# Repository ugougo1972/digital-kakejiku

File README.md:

# digital-kakejiku

**タイトル**  
digital-kakejiku

**最終更新**  
2026-07-15

**文書版**  
vNext 1.3

**STATUS**  
FINALIZED

**責務**  
本書は digital-kakejiku プロジェクトの入口となる文書であり、プロジェクトの目的、全体構成、開発状況、文書体系への導線を提供する。

**Single Source**  
本書はプロジェクト概要および文書体系の入口を管理する唯一の文書である。詳細仕様は各設計文書を参照し、本書へ重複記載しない。

---

# 対象読者

- プロジェクトオーナー
- ハードウェア設計者
- ソフトウェア設計者
- GAS開発者
- 保守担当者
- 新規参画者

---

# 関連文書

## 前提

- docs/00_PROJECT_CONVENTIONS.md

## 参照

- CURRENT_STATUS.md
- ROADMAP.md

## 関連

- docs/01_HARDWARE_OVERVIEW.md
- docs/02_SOFTWARE_OVERVIEW.md
- docs/03_LOG_FORMAT.md
- docs/04_STATE_MACHINE.md
- docs/05_WIRING_DIAGRAM.md
- docs/06_GAS_API_SPEC.md
- docs/07_DISPLAY_UI_SPEC.md
- docs/08_POWER_ARCHITECTURE.md
- docs/09_SPI_RESOURCE_CONTROL.md
- docs/10_CALENDAR_POEM_SUBSYSTEM.md
- docs/11_SECURITY_MANAGEMENT.md
- docs/12_CONFIGURATION_MANAGEMENT.md
- docs/13_GAS_OPERATION_POLICY.md
- docs/14_SPREADSHEET_SCHEMA.md
- docs/15_GAS_IMPLEMENTATION_GUIDE.md
- docs/16_TESTING_STRATEGY.md
- docs/17_TROUBLESHOOTING.md
- docs/18_GAS_RETRY_STRATEGY.md
- docs/19_GEMINI_PROMPT_SPECIFICATION.md

## 後続

本リポジトリを利用するすべての設計・実装・試験・保守作業

---

# 1. プロジェクト概要

## 1.1 概要

digital-kakejiku は、環境観測、暦情報表示、AIによる詩生成を組み合わせた据置型情報表示システムである。

ESP32マイコンを中心として各種環境センサーから取得した情報を Google Apps Script および Google Spreadsheet に蓄積し、必要に応じて AI による文章生成を行い、7.5inch E-Paper に表示する。

本プロジェクトは長期間の安定運用、保守性、拡張性およびドキュメント駆動開発を重視する。

---

## 1.2 プロジェクト目的

本プロジェクトでは以下を目的とする。

- 環境情報の継続的な観測
- 暦情報の表示
- AI生成コンテンツの活用
- 長期運用可能な据置型システムの構築
- 保守性・拡張性を考慮した設計

---

# 2. システム概要

## 2.1 全体構成

```text
環境センサー
        │
        ▼
XIAO ESP32S3 Plus
        │
     HTTPS
        │
        ▼
Google Apps Script
        │
        ▼
Google Spreadsheet
        │
        ▼
Gemini
        │
        ▼
7.5inch E-Paper
```

各コンポーネントの詳細仕様は個別設計書で管理する。

---

## 2.2 システム構成

本システムは以下の主要コンポーネントで構成される。

### ハードウェア

- 本体基板
- 電源基板
- OLED操作基板

### ソフトウェア

- ESP32 Firmware
- Google Apps Script
- Google Spreadsheet
- Gemini

---

## 2.3 主な特徴

- 据置型観測システム
- UPS電源構成
- 7.5inch E-Paper表示
- Google Apps Script連携
- Google Spreadsheet連携
- AIによる詩生成
- 保守用OLEDコンソール
- モジュール交換可能構造
- ファンレス自然空冷

---

# 3. 開発状況

本書では概要のみを示す。

現在の詳細な進捗、完了状況、課題および開発優先順位は **CURRENT_STATUS.md** を正式情報とする。

現在の開発フェーズは以下のとおりである。

|項目|状態|
|---|---|
|開発フェーズ|IN_PROGRESS|
|電源基板PoC|COMPLETED|
|本体基板設計|IN_PROGRESS|
|筐体設計|IN_PROGRESS|
|GAS実装|IN_PROGRESS|
|文書体系整備|IN_PROGRESS|

---

# 4. システム設計方針

本プロジェクトでは以下の設計方針を採用する。

- ドキュメント駆動開発
- モジュール構成
- 保守性優先
- 拡張性優先
- 長期運用を前提とした設計
- GitHubを正式設計情報とする

設計規約の詳細は **00_PROJECT_CONVENTIONS.md** を参照する。

---

# 5. 文書体系

## 5.1 基準文書

以下の4文書をプロジェクト全体の基準文書とする。

|文書|責務|
|---|---|
|README.md|プロジェクト概要・入口|
|CURRENT_STATUS.md|現在の開発状況|
|ROADMAP.md|中長期開発計画|
|docs/00_PROJECT_CONVENTIONS.md|共通規約|

---

## 5.2 設計文書

|文書|内容|
|---|---|
|01_HARDWARE_OVERVIEW|ハードウェア全体設計|
|02_SOFTWARE_OVERVIEW|ソフトウェア全体設計|
|03_LOG_FORMAT|ログ仕様|
|04_STATE_MACHINE|状態遷移|
|05_WIRING_DIAGRAM|配線仕様|
|06_GAS_API_SPEC|GAS API仕様|
|07_DISPLAY_UI_SPEC|表示仕様|
|08_POWER_ARCHITECTURE|電源設計|
|09_SPI_RESOURCE_CONTROL|SPI資源管理|
|10_CALENDAR_POEM_SUBSYSTEM|暦・詩生成|
|11_SECURITY_MANAGEMENT|セキュリティ|
|12_CONFIGURATION_MANAGEMENT|設定管理|
|13_GAS_OPERATION_POLICY|GAS運用|
|14_SPREADSHEET_SCHEMA|Spreadsheet設計|
|15_GAS_IMPLEMENTATION_GUIDE|GAS実装|
|16_TESTING_STRATEGY|試験方針|
|17_TROUBLESHOOTING|障害対応|
|18_GAS_RETRY_STRATEGY|リトライ設計|
|19_GEMINI_PROMPT_SPECIFICATION|Geminiプロンプト仕様|

---

# 6. リポジトリ運用方針

設計・実装・試験・運用に関する情報は GitHub リポジトリで管理する。

設計変更時は以下の順序で更新する。

1. 設計文書更新
2. 関連文書との整合性確認
3. GitHub反映
4. 実装
5. 試験

設計書より先に実装を変更する運用は行わない。

---

# 7. 開発ロードマップ

本書では概要のみを示す。

詳細なマイルストーン、計画および将来構想は **ROADMAP.md** を正式情報とする。

---

# 8. 現在未定義の事項

以下は本書では定義しない。

- リリース計画
- バージョン採番規則
- Git運用詳細
- ブランチ運用
- Commit Message規則

必要となった時点で関連文書に追加する。

---

# CHANGE LOG

|日付|内容|
|---|---|
|2026-07-15|vNext 1.3として全面刷新。READMEをプロジェクト入口文書へ再設計し、Single Source of Truthに基づきCURRENT_STATUS、ROADMAP、00_PROJECT_CONVENTIONSとの責務を明確化。|
|2026-07-14|初版更新。|

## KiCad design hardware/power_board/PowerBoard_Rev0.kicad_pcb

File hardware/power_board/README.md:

# digital-kakejiku PowerBoard Rev.0

## 1. 位置付け

本データは、digital-kakejiku 電源基板PoCの実測結果と、以下の確定済み構成を基に作成した
**KiCad 10取込用の初期設計データ**です。

```text
USB Type-C
    │
   PTC
    │
  IP5306
    │
DMG2305UX-13
    │
  5V_BUS
    │
 TPS63802
    │
 3.3V_OUT
```

## 2. 重要な注意

本データは **JLCPCBへそのまま発注できる最終製造版ではありません**。

理由は、実際に使用する以下の市販モジュールについて、外形寸法・端子ピッチ・穴径が
リポジトリ文書だけでは確定できないためです。

- USB Type-Cブレークアウト基板
- IP5306モジュール
- TPS63802モジュール
- 18650接続コネクタ
- 本体基板接続用10ピンヘッダーの実装形態

現在のPCBデータでは、これらを汎用2.54 mmピッチのスルーホール部品として仮配置しています。
実物を採寸し、フットプリントを確定してから製造データを生成してください。

## 3. 収録ファイル

|ファイル|用途|
|---|---|
|`PowerBoard_Rev0.sch`|KiCad legacy回路図。KiCad 10で開き、`.kicad_sch`として保存してください。|
|`PowerBoard_Rev0.kicad_pcb`|KiCad PCB初期レイアウト。部品配置・ネット・外形を収録しています。|
|`PowerBoard_Rev0.kicad_pro`|KiCadプロジェクト設定の最小ファイルです。|
|`BOM.csv`|初期部品表です。|
|`NETLIST.csv`|ネット接続表です。|
|`FOOTPRINT_CONFIRMATION.md`|実物採寸が必要な項目の一覧です。|
|`JLCPCB_CHECKLIST.md`|Gerber生成前および発注前の確認表です。|

## 4. KiCad 10での開始手順

1. ZIPを展開します。
2. KiCad 10を起動します。
3. `PowerBoard_Rev0.sch`を回路図エディターで開きます。
4. 変換確認が表示された場合は、KiCad 10形式で保存します。
5. 保存名を `PowerBoard_Rev0.kicad_sch` とします。
6. `PowerBoard_Rev0.kicad_pcb`をPCBエディターで開きます。
7. フットプリント実寸を確認・修正します。
8. 回路図からPCBを更新します。
9. ERC・DRCを実行します。
10. エラーおよび未確認警告が残る状態ではJLCPCBへ発注しません。

## 5. 確定済み10ピン電源インターフェース

|ピン|信号|
|---:|---|
|1|5V_OUT|
|2|5V_GND|
|3|5V_OUT|
|4|5V_GND|
|5|3.3V_OUT|
|6|3.3V_GND|
|7|3.3V_OUT|
|8|Battery_SENSE|
|9|5V_SENSE|
|10|SENSE_GND|

## 6. GND方針

- 5V_GND、3.3V_GND、SENSE_GNDは電源基板上で意図的に別ネットとしています。
- 本体基板側のXIAO近傍で一点接続する設計方針です。
- これは電気的絶縁ではなく、リターン経路整理によるノイズ低減を目的とします。
- 使用モジュール内部でGNDが導通している可能性は、実物の導通測定で確認してください。

## 7. Rev.0で仮定した回路定数

|項目|値|
|---|---:|
|5V_SENSE上側抵抗|150 kΩ|
|5V_SENSE下側抵抗|100 kΩ|
|Battery_SENSE上側抵抗|100 kΩ|
|Battery_SENSE下側抵抗|100 kΩ|
|DMG2305UX Gate抵抗|100 kΩ|
|TPS63802入力高周波C|0.1 µF|
|TPS63802入力バルクC|470 µF|
|TPS63802出力高周波C|0.1 µF|
|TPS63802出力バルクC|220 µF|

## 8. 未確認事項

- PTCの定格・型番・実装ピッチ
- IP5306モジュールの端子順、端子間隔、基板外形
- TPS63802モジュールの端子順、端子間隔、基板外形
- DMG2305UX-13の採用フットプリントと実装方向
- USB Type-C基板の端子順、端子間隔、基板外形
- 18650コネクタのシリーズと極性
- 取付穴位置および筐体との干渉
- JLCPCBの製造設定
- ERC・DRC結果

## 9. 製造禁止条件

以下のいずれかに該当する場合、Gerber発注を行わないでください。

- 実物採寸が未完了
- モジュールの端子順が未確認
- MOSFETのS/G/D対応が未確認
- ERCまたはDRCに未解決エラーがある
- 3系統GNDの意図と実モジュール内部導通が未評価
- 1:1印刷による部品実装確認が未実施

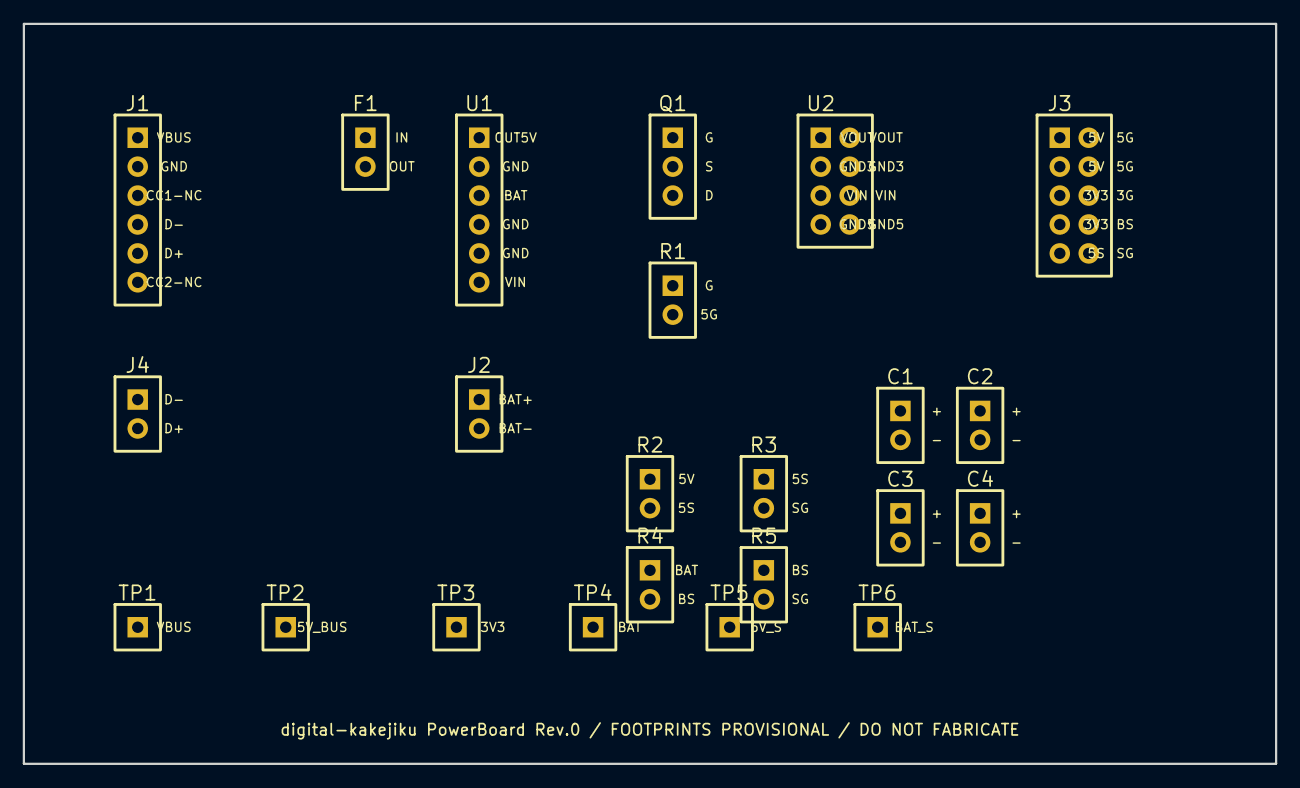
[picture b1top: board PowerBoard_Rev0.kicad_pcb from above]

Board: 2 copper layers, 110.0 x 65.0 mm, 23 parts (0 on the bottom side), 15 nets, no tracks yet.

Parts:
C1: 0.1u; C1
C2: 470u; C2
C3: 0.1u; C3
C4: 220u; C4
F1: PTC; F1
J1: USB-C BREAKOUT; J1
J2: 18650; J2
J3: MAIN POWER 10PIN; J3
J4: USB DATA; J4
Q1: DMG2305UX-13; Q1
R1: 100k; R1
R2: 150k; R2
R3: 100k; R3
R4: 100k; R4
R5: 100k; R5
TP1: VBUS; TP1
TP2: 5V_BUS; TP2
TP3: 3V3; TP3
TP4: BAT; TP4
TP5: 5V_S; TP5
TP6: BAT_S; TP6
U1: IP5306 MODULE; U1
U2: TPS63802 MODULE; U2

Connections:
3V3_GND: C3.2, C4.2, J3.6, U2.3, U2.4
3V3_OUT: C3.1, C4.1, J3.5, J3.7, TP3.1, U2.1, U2.2
5V_BUS: C1.1, C2.1, J3.1, J3.3, Q1.3, R2.1, TP2.1, U2.5, U2.6
5V_GND: J1.2, J1.3, J1.6, J3.2, J3.4, R1.2, U1.2, U1.4, U1.5
5V_SENSE: J3.9, R2.2, R3.1, TP5.1
BAT: J2.1, R4.1, TP4.1, U1.3
BATTERY_SENSE: J3.8, R4.2, R5.1, TP6.1
OUT_5V: Q1.2, U1.1
Q_GATE: Q1.1, R1.1
SENSE_GND: J3.10, R3.2, R5.2
TPS_IN_GND: C1.2, C2.2, U2.7, U2.8
USB_D+: J1.5, J4.2
USB_D-: J1.4, J4.1
VBUS: F1.1, J1.1, TP1.1
VIN_IP5306: F1.2, U1.6

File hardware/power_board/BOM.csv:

Ref,品名,規格/フットプリント,確認状況,備考
J1,USB Type-C breakout,1x6 2.54mm provisional,未確認,CC抵抗実装済み基板を使用
F1,PTC fuse,THT radial provisional,未確認,定格・ピッチ未確認
U1,IP5306 module,1x6 2.54mm provisional,未確認,端子順 OUT_5V/GND/BAT/GND/GND/VIN を仮定
Q1,DMG2305UX-13,SOT-23,要確認,S/G/Dと基板方向をデータシート・実物で確認
R1,Gate pull-down,100kΩ 0805,確定値,Gate→5V_GND
U2,TPS63802 module,2x4 2.54mm provisional,未確認,VOUT×2/GND×2、VIN×2/GND×2を仮定
C1,Input ceramic,0.1µF 0805,確定値,TPS63802入力直近
C2,Input bulk,470µF radial,確定値,耐圧未確認
C3,Output ceramic,0.1µF 0805,確定値,TPS63802出力直近
C4,Output bulk,220µF radial,確定値,耐圧未確認
R2,5V_SENSE upper,150kΩ 0805,確定値,5V_BUS→5V_SENSE
R3,5V_SENSE lower,100kΩ 0805,確定値,5V_SENSE→SENSE_GND
R4,Battery_SENSE upper,100kΩ 0805,確定値,BAT→Battery_SENSE
R5,Battery_SENSE lower,100kΩ 0805,確定値,Battery_SENSE→SENSE_GND
J2,18650 connector,1x2 2.54mm provisional,未確認,極性を実物確認
J3,Main board power header,2x5 2.54mm,仮確定,ピン割当はREADME参照
J4,USB D+/D- header,1x2 2.54mm,仮確定,本体基板へのUSB通信
TP1,VBUS test point,1pin THT,確定用途,
TP2,5V_BUS test point,1pin THT,確定用途,
TP3,3.3V_OUT test point,1pin THT,確定用途,
TP4,BAT test point,1pin THT,確定用途,
TP5,5V_SENSE test point,1pin THT,確定用途,
TP6,Battery_SENSE test point,1pin THT,確定用途,

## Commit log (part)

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2026-05-27 DOC:README_Release
2026-05-27 doc:NewRelease
2026-05-27 doc:UpDate
2026-05-27 gs:NEW
2026-05-27 doc:ReNewal
2026-05-30 DOC:Phase1.5
2026-05-31 DOC:電源アーキテクチャ確定(IP5306 + TPS63802 + UPS)
2026-05-31 DOC:ReNew
2026-06-02 Doc:刷新
2026-06-02 DOC:NEW
2026-06-19 Doc:Ver2
2026-06-19 Doc:2.01
2026-06-19 Doc:2.02
2026-06-19 doc:2.03
2026-06-19 DOC:2.04
2026-06-19 doc:2.1
2026-06-20 DOC:3.0
2026-06-20 DOC:3.1
2026-06-20 Doc:SZK
2026-06-25 DOC:MinorUpDate
2026-06-28 DOC:Power Renewal
